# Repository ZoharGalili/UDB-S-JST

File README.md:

# Modified Unified Daughterboard S 

## Changes 

- switched to the reliable JST connector.
- replaced esd chip to the SRV05-4.
- changed the fotprint to 0805.
- switched to a 2 layer pcb.

## Why Change?

i made a custom keyboard design a while ago with the UDS-S and i hand soldered all the components myself because im broke. 
there were a few problems i encountered with the doughterboard:
- the board was extremely difficult to solder. expecially the tiny esd chip.
- the ezmate molex connector is trash. after soldering up the board the connector kept snapping off the board.
i dont know why the connector kept snapping off but the fact that it pulls up to dissconnect only encourages its snapping off.
- i switched to 2 layer just because i didnt use more than the 2 layers when routing.

honestly i dont know if ill make this design but well see...

## Previews

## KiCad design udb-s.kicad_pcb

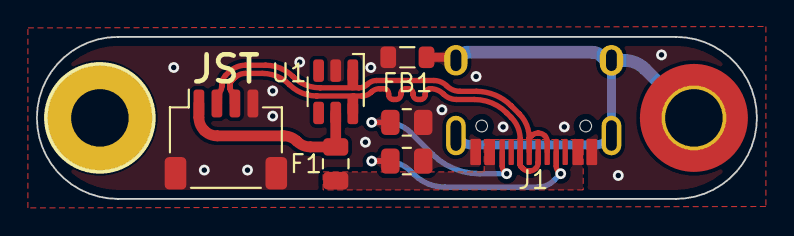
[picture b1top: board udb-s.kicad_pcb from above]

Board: 2 copper layers, 40.0 x 9.0 mm, 9 parts (0 on the bottom side), 8 nets.

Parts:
F1: SMD0805-050-16V; Fuse_0805_2012Metric
FB1: L_0805_2012Metric
H1: MountingHole; MountingHole_3.2mm_M3_DIN965_Pad_TopBottom
H2: MountingHole; MountingHole_3.2mm_M3_DIN965_Pad_TopOnly
J1: TYPE-C-31-M-12; HRO-TYPE-C-31-M-12-Assembly
JST: WAFER-SH1.0-4PWB; JST_SH_SM04B-SRSS-TB_1x04-1MP_P1.00mm_Horizontal
R1, R2: 5.1k; R_0805_2012Metric
U1: SRV05-4; SOT-23-6-routable

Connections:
5V: F1.2, JST.1, U1.5 (VP)
D+: J1.A6 (D+), J1.B6 (D+), JST.3, U1.6 (IO4)
D-: J1.A7 (D-), J1.B7 (D-), JST.2, U1.1 (IO1)
GND: FB1.2, J1.A1 (GND), J1.B1 (GND), JST.4, JST.MP (MountPin), R1.1, R2.2, U1.2 (VN)
GNDPWR: FB1.1, H1.1, J1.S1 (SHIELD)
unnamed: J1.A5 (CC1), R1.2
unnamed: J1.B5 (CC2), R2.1
VBUS: F1.1, J1.A4 (VBUS), J1.B4 (VBUS)

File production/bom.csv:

Designator,Footprint,Quantity,Value,LCSC Part #
F1,0805,1,SMD0805-050-16V,
FB1,0805,1,~,
J1,HRO-TYPE-C-31-M-12-Assembly,1,TYPE-C-31-M-12,
J2,JST_SH_SM04B-SRSS-TB_1x04-1MP_P1.00mm_Horizontal,1,WAFER-SH1.0-4PWB,
"R1, R2",0805,2,5.1k,
U1,SOT-23-6-routable,1,SRV05-4,

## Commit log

2025-06-09 the pcb
    changed everything i wanted
2025-06-09 readme
    little readme yay
2025-06-09 fixed the images
2025-06-09 generated production files
2025-06-14 BOM done
2025-08-13 fixed usb traces + teardrops
    the usb traces were only connected to two of the pins on the usb connector
2025-08-14 made production files + BOM
    generated the production files and filled out the BOM using lcsc components
2025-08-15 cheaper jst connector
    changed to a cheaper jst connector (XUNPU WAFER-SH1.0-4PWB)
2025-10-04 final tweeks
    the USB pair impedance is now closer to 90 and has less interruptions in its reference ground plane
2025-10-04 updated photos
    updated the photos in the readme
2025-10-05 swapped to SRV05-4
    swapped the esd chip to the SRV05-4 and removed the singular diode because its built into the esd chip
2025-11-21 usb length matching
    made the usb line length matching as well as some other minor stuff
2025-11-30 updated renders
    updated the renders of the board to those that are the newest version
